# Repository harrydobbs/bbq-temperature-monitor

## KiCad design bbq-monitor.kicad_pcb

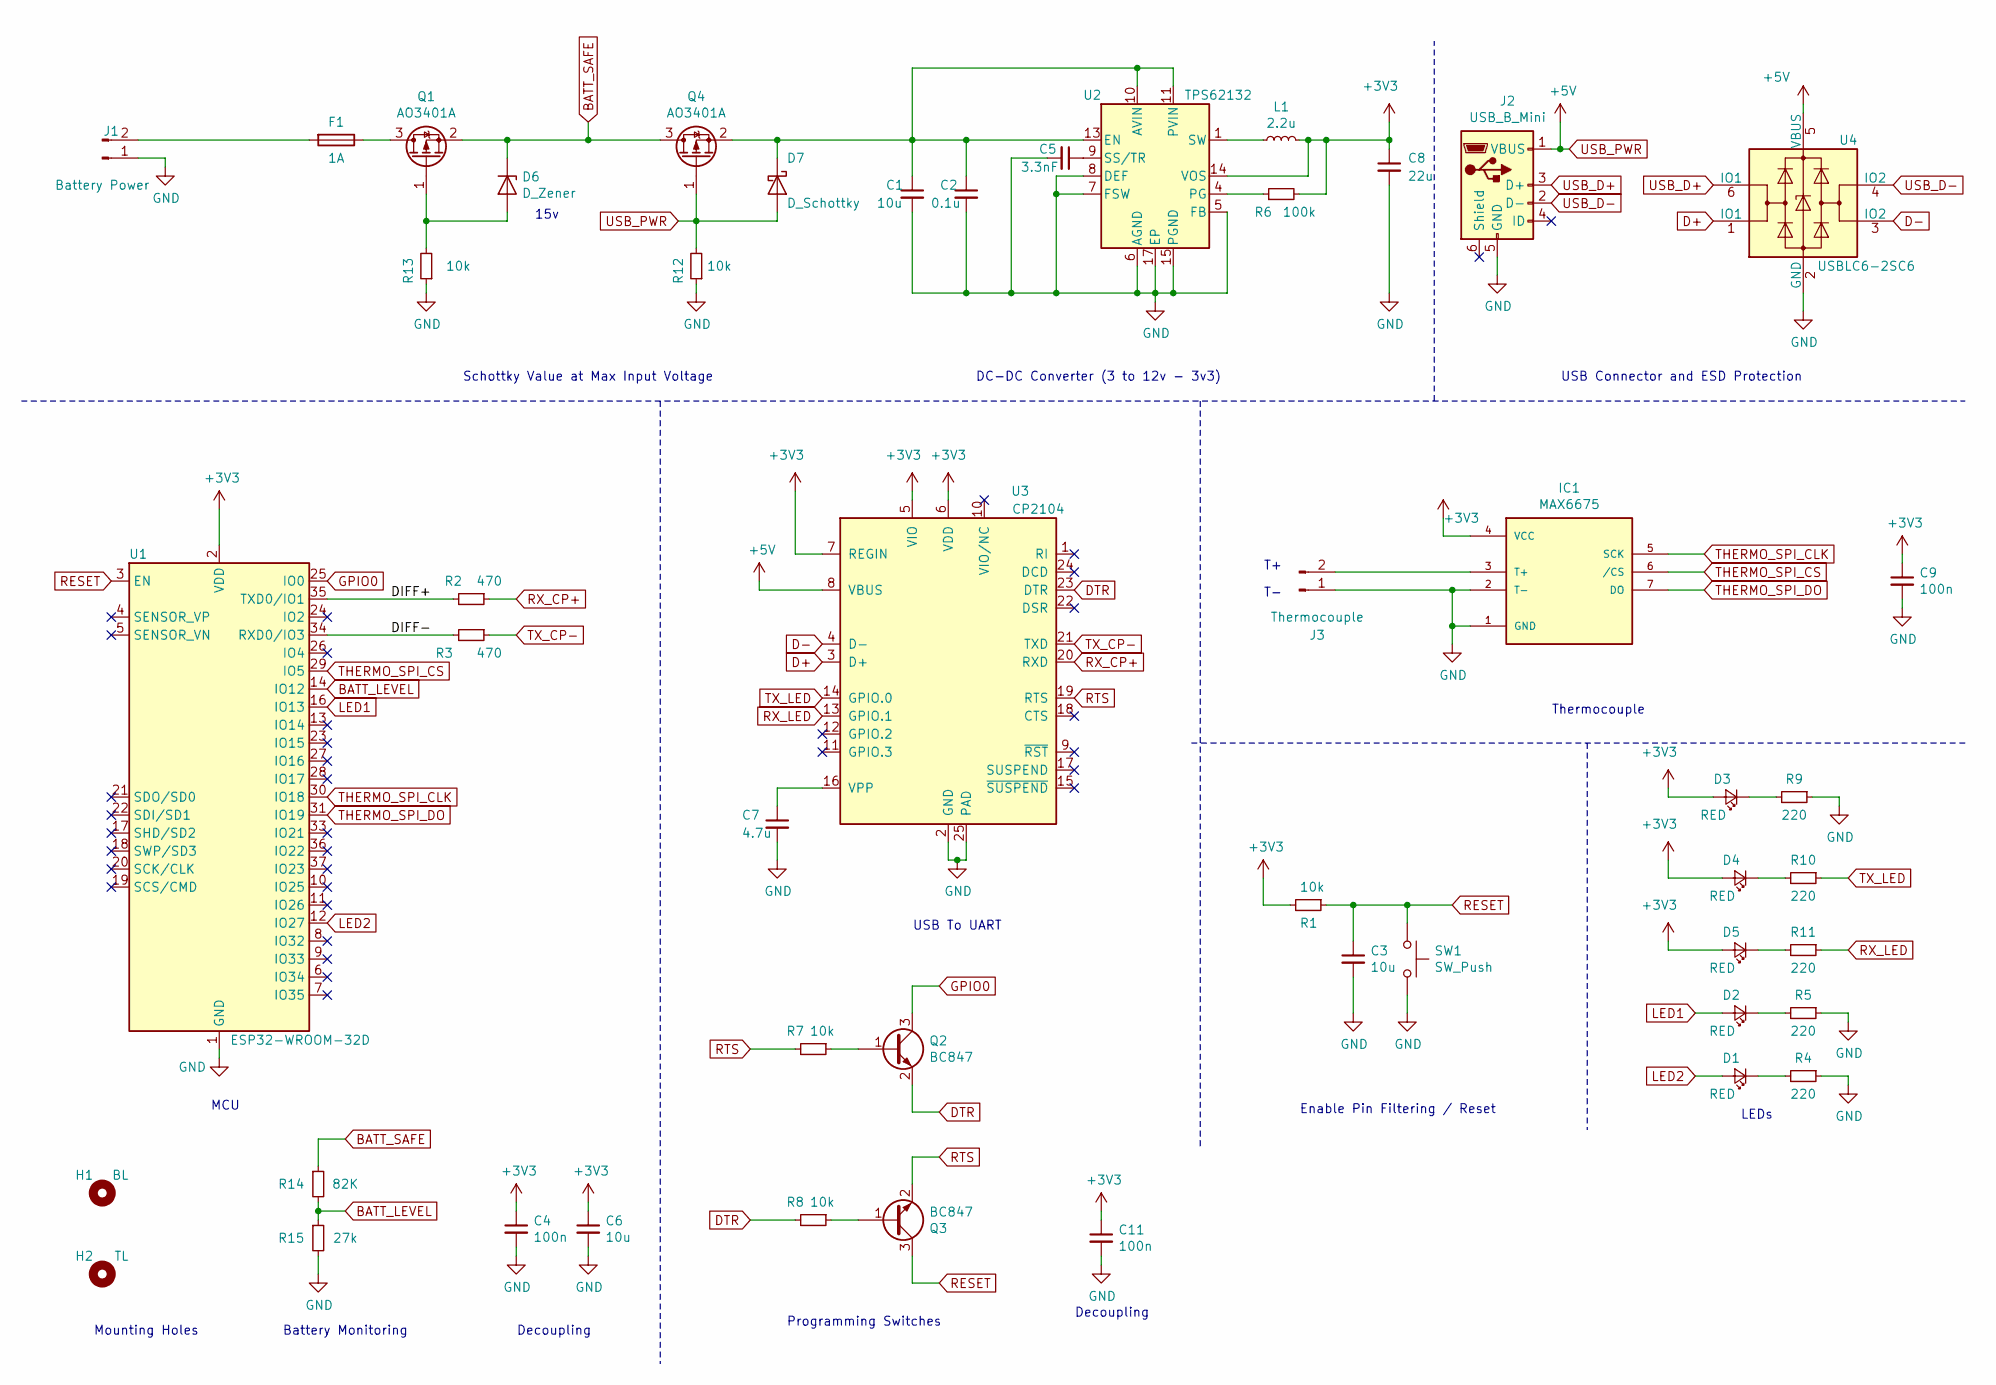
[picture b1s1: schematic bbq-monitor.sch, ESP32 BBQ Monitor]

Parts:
C1, C3, C6: 10u; C_0603_1608Metric; LCSC Part # C96446
C2: 0.1u; C_0603_1608Metric
C4, C9, C11: 100n; C_0603_1608Metric; LCSC Part # C14663
C5: 3.3nF; C_0603_1608Metric
C7: 4.7u; C_0603_1608Metric
C8: 22u; C_0603_1608Metric
D1, D2, D3, D4, D5: RED; LED_0603_1608Metric; LCSC Part # C2286
D6: D_Zener; D_1206_3216Metric
D7: D_Schottky; D_1206_3216Metric
F1: 1A; Fuse_1206_3216Metric
H1: BL; MountingHole_3.2mm_M3
H2: TL; MountingHole_3.2mm_M3
IC1: MAX6675; SO08
J1: Battery Power; RS-Pro-5mm-Pitch-2-Pin-Terminal
J2: USB_B_Mini; USB_Mini-B_Wuerth_65100516121_Horizontal
J3: Thermocouple; RS-Pro-5mm-Pitch-2-Pin-Terminal
L1: 2.2u; L_1210_3225Metric
Q1, Q4: AO3401A; SOT-23; LCSC Part # C15127
Q2, Q3: BC847; SOT-23; LCSC Part # C8664
R1, R7, R8, R12, R13: 10k; R_0603_1608Metric; LCSC Part # C25804
R2, R3: 470; R_0603_1608Metric; LCSC Part # C23179
R4, R5, R9, R10, R11: 220; R_0603_1608Metric; LCSC Part # C22962
R6: 100k; R_0603_1608Metric
R14: 82K; R_0603_1608Metric
R15: 27k; R_0603_1608Metric
SW1: SW_Push; SW_Push_1P1T_NO_6x6mm_H9.5mm
U1: ESP32-WROOM-32D; ESP32-WROOM-32; LCSC Part # C473012
U2: TPS62132; VQFN-16-1EP_3x3mm_P0.5mm_EP1.68x1.68mm_ThermalVias; LCSC Part # C81563
U3: CP2104; QFN-24-1EP_4x4mm_P0.5mm_EP2.6x2.6mm; LCSC Part # C47742 Copy
U4: USBLC6-2SC6; SOT-23-6; LCSC Part # C2827654

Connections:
+3V3: C4.1, C6.1, C8.1, C9.1, C11.1, D3.2 (A), D4.2 (A), D5.2 (A), IC1.4 (VCC), L1.2, R1.2, R6.2, U1.2 (VDD), U2.14 (VOS), U3.5 (VIO), U3.6 (VDD), U3.7 (REGIN)
/DIFF+: R2.2, U1.35 (TXD0/IO1)
/DIFF-: R3.2, U1.34 (RXD0/IO3)
BATT_LEVEL: R14.2, R15.1, U1.14 (IO12)
BATT_SAFE: D6.1 (K), Q1.2 (S), Q4.3 (D), R14.1
D+: U3.3 (D+), U4.1 (IO1)
D-: U3.4 (D-), U4.3 (IO2)
DTR: Q2.2 (E), R8.2, U3.23 (DTR)
GND: C1.2, C2.2, C3.2, C4.2, C5.2, C6.2, C7.2, C8.2, C9.2, C11.2, IC1.1 (GND), IC1.2 (T-), J1.1, J2.5 (GND), J3.1, R4.1, R5.1, R9.1, R12.1, R13.1, R15.2, SW1.2, U1.1 (GND), U1.15 (GND), U1.38 (GND), U1.39 (GND), U2.5 (FB), U2.6 (AGND), U2.7 (FSW), U2.8 (DEF), U2.15 (PGND), U2.16 (PGND), U2.17 (EP), U3.2 (GND), U3.25 (PAD), U4.2 (GND)
GPIO0: Q2.3 (C), U1.25 (IO0)
LED1: D2.2 (A), U1.16 (IO13)
LED2: D1.2 (A), U1.12 (IO27)
unnamed: C1.1, C2.1, D7.1 (K), Q4.2 (S), U2.10 (AVIN), U2.11 (PVIN), U2.12 (PVIN), U2.13 (EN)
unnamed: C5.1, U2.9 (SS/TR)
unnamed: C7.1, U3.16 (VPP)
unnamed: D1.1 (K), R4.2
unnamed: D2.1 (K), R5.2
unnamed: D3.1 (K), R9.2
unnamed: D4.1 (K), R10.2
unnamed: D5.1 (K), R11.2
unnamed: D6.2 (A), Q1.1 (G), R13.2
unnamed: F1.1, Q1.3 (D)
unnamed: F1.2, J1.2
unnamed: IC1.3 (T+), J3.2
unnamed: L1.1, U2.1 (SW), U2.2 (SW), U2.3 (SW)
unnamed: Q2.1 (B), R7.1
unnamed: Q3.1 (B), R8.1
unnamed: R6.1, U2.4 (PG)
RESET: C3.1, Q3.3 (C), R1.1, SW1.1, U1.3 (EN)
RTS: Q3.2 (E), R7.2, U3.19 (RTS)
RX_CP+: R2.1, U3.20 (RXD)
RX_LED: R11.1, U3.13 (GPIO.1)
THERMO_SPI_CLK: IC1.5 (SCK), U1.30 (IO18)
THERMO_SPI_CS: IC1.6 (/CS), U1.29 (IO5)
THERMO_SPI_DO: IC1.7 (DO), U1.31 (IO19)
TX_CP-: R3.1, U3.21 (TXD)
TX_LED: R10.1, U3.14 (GPIO.0)
USB_D+: J2.3 (D+), U4.6 (IO1)
USB_D-: J2.2 (D-), U4.4 (IO2)
USB_PWR: D7.2 (A), J2.1 (VBUS), Q4.1 (G), R12.2, U3.8 (VBUS), U4.5 (VBUS)

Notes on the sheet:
Enable Pin Filtering / Reset
USB To UART
MCU
DC-DC Converter (3 to 12v - 3v3)
Programming Switches
Decoupling
Thermocouple
USB Connector and ESD Protection
Mounting Holes
Battery Monitoring
LEDs
Schottky Value at Max Input Voltage
15v

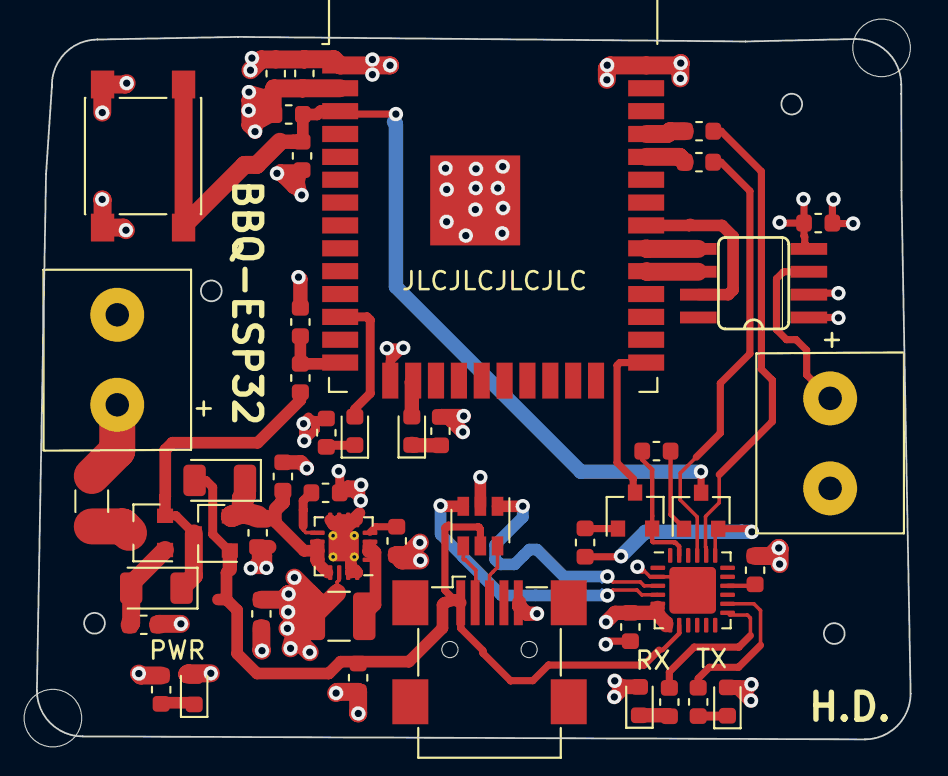
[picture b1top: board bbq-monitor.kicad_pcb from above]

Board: 4 copper layers, 48.5 x 39.0 mm, 49 parts (0 on the bottom side), 40 nets.

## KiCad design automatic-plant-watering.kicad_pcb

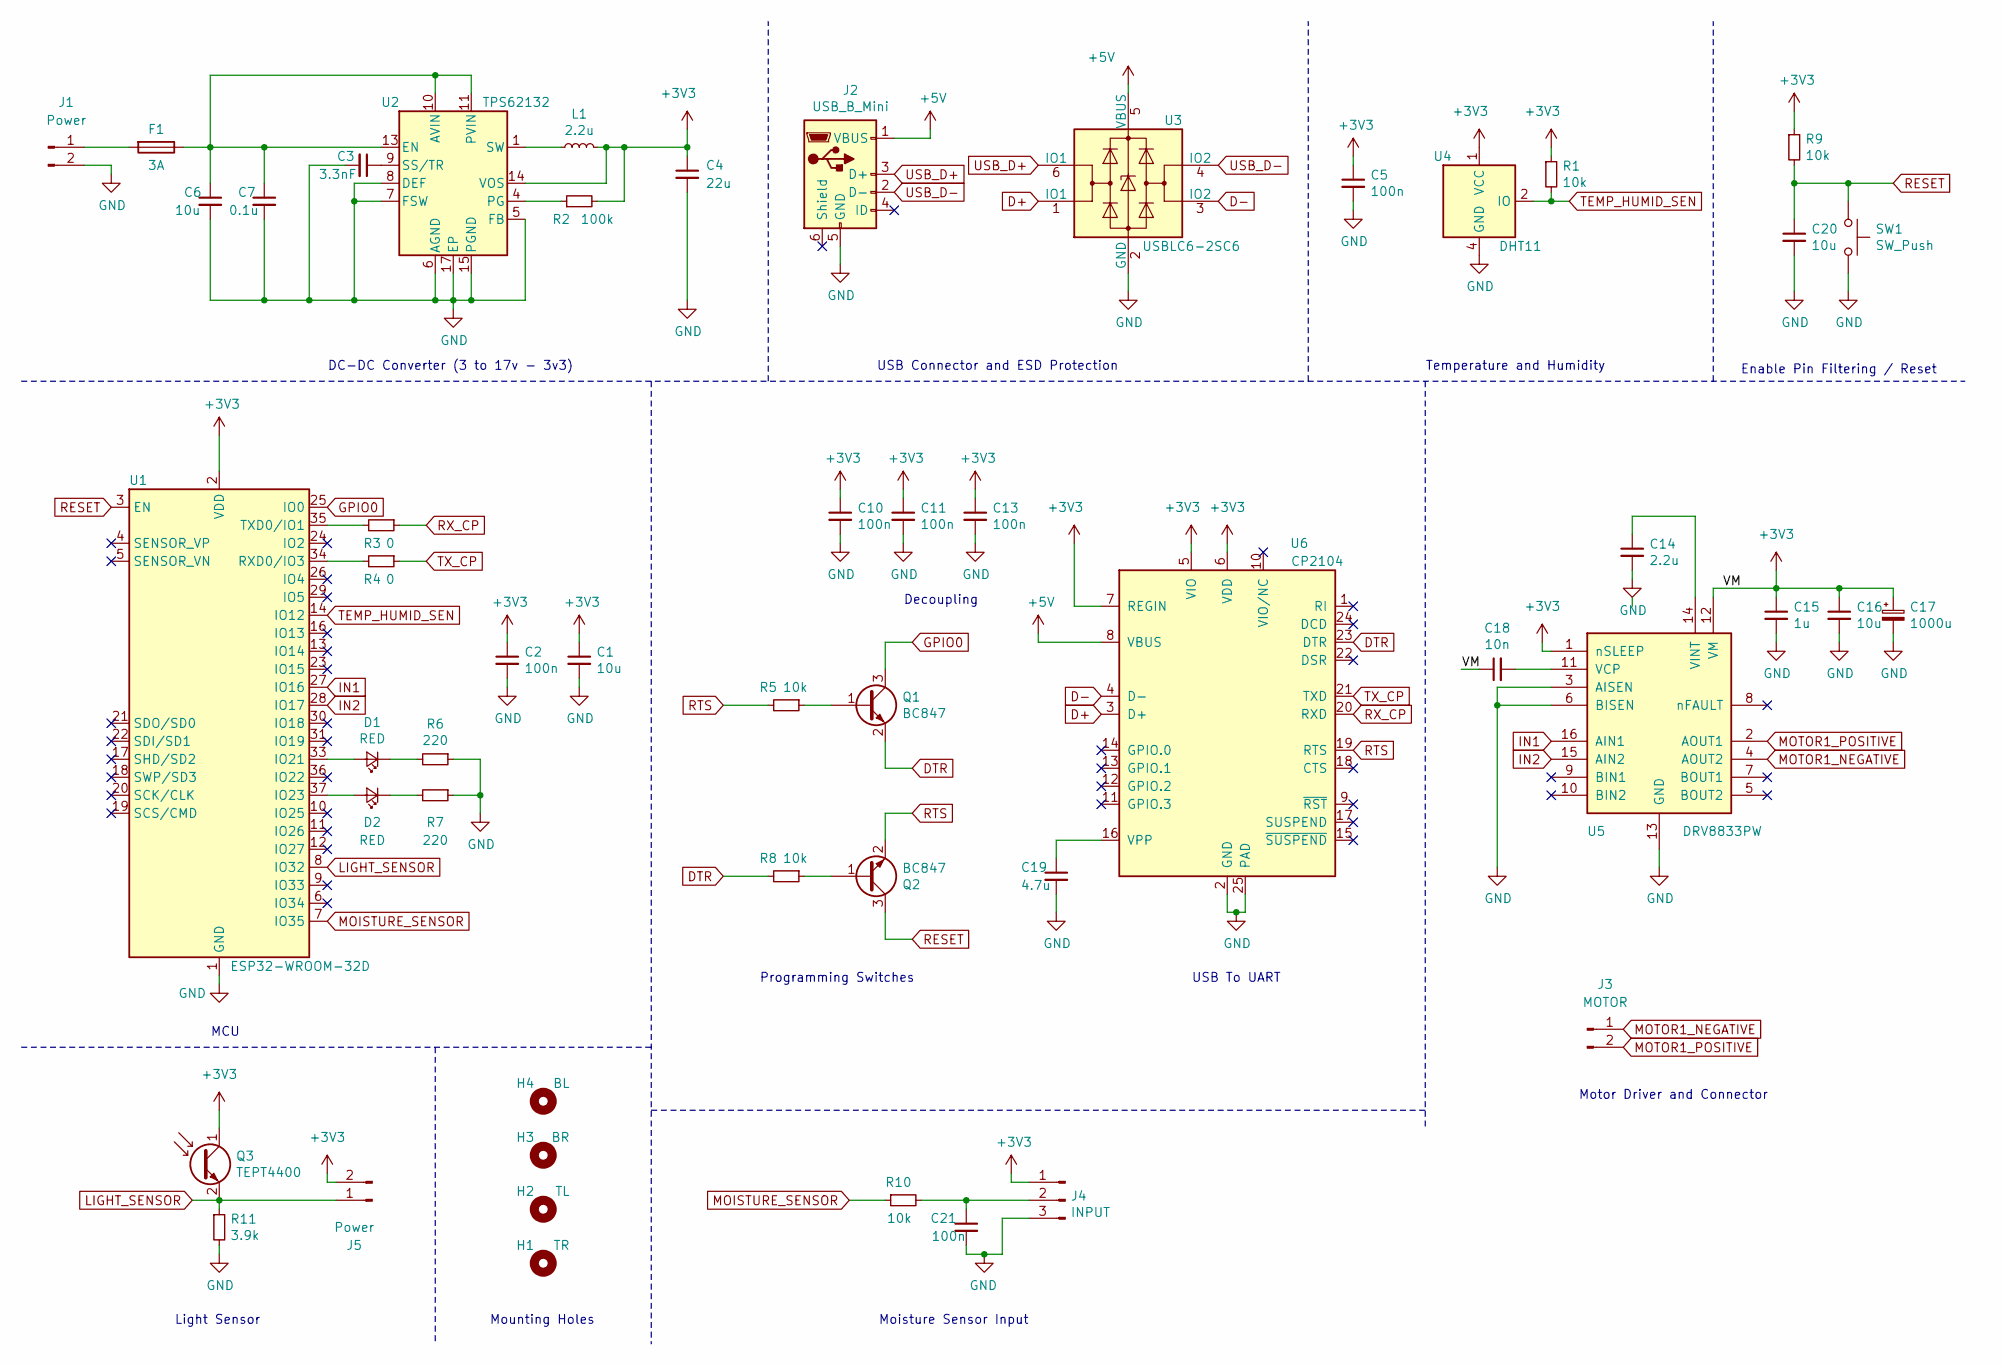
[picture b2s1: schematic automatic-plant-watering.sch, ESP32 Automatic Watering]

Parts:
C1, C6, C16, C20: 10u; C_0603_1608Metric
C2, C5, C10, C11, C13, C21: 100n; C_0603_1608Metric
C3: 3.3nF; C_0603_1608Metric
C4: 22u; C_0603_1608Metric
C7: 0.1u; C_0603_1608Metric
C14: 2.2u; C_0603_1608Metric
C15: 1u; C_0603_1608Metric
C17: 1000u; CP_Elec_10x10
C18: 10n; C_0603_1608Metric
C19: 4.7u; C_0603_1608Metric
D1, D2: RED; LED_0603_1608Metric
F1: 3A; Fuse_1206_3216Metric
H1: TR; MountingHole_4.3mm_M4_Pad_Via
H2: TL; MountingHole_4.3mm_M4_Pad_Via
H3: BR; MountingHole_4.3mm_M4_Pad_Via
H4: BL; MountingHole_4.3mm_M4_Pad_Via
J1, J5: Power; Molex_KK-254_AE-6410-02A_1x02_P2.54mm_Vertical
J2: USB_B_Mini; USB_Mini-B_Wuerth_65100516121_Horizontal
J3: MOTOR; Molex_KK-254_AE-6410-02A_1x02_P2.54mm_Vertical
J4: INPUT; Molex_KK-254_AE-6410-03A_1x03_P2.54mm_Vertical
L1: 2.2u; L_1210_3225Metric
Q1, Q2: BC847; SOT-23
Q3: TEPT4400; LED_D3.0mm_Clear
R1, R5, R8, R9, R10: 10k; R_0603_1608Metric
R2: 100k; R_0603_1608Metric
R3, R4: 0; R_0603_1608Metric
R6, R7: 220; R_0603_1608Metric
R11: 3.9k; R_0603_1608Metric
SW1: SW_Push; SW_Push_1P1T_NO_6x6mm_H9.5mm
U1: ESP32-WROOM-32D; ESP32-WROOM-32
U2: TPS62132; VQFN-16-1EP_3x3mm_P0.5mm_EP1.68x1.68mm_ThermalVias
U3: USBLC6-2SC6; SOT-23-6
U4: DHT11; Aosong_DHT11_5.5x12.0_P2.54mm
U5: DRV8833PW; TSSOP-16_4.4x5mm_P0.65mm
U6: CP2104; QFN-24-1EP_4x4mm_P0.5mm_EP2.6x2.6mm

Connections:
+3V3: C1.1, C2.1, C4.1, C5.1, C10.1, C11.1, C13.1, C15.1, C16.1, C17.1, C18.1, J4.1, J5.2, L1.2, Q3.1 (C), R1.1, R2.2, R9.1, U1.2 (VDD), U2.14 (VOS), U4.1 (VCC), U5.1 (nSLEEP), U5.12 (VM), U6.5 (VIO), U6.6 (VDD), U6.7 (REGIN)
+5V: J2.1 (VBUS), U3.5 (VBUS), U6.8 (VBUS)
D+: U3.1 (IO1), U6.3 (D+)
D-: U3.3 (IO2), U6.4 (D-)
DTR: Q1.2 (E), R8.2, U6.23 (DTR)
GND: C1.2, C2.2, C3.2, C4.2, C5.2, C6.2, C7.2, C10.2, C11.2, C13.2, C14.2, C15.2, C16.2, C17.2, C19.2, C20.2, C21.2, J1.2, J2.5 (GND), J4.3, R6.1, R7.1, R11.2, SW1.2, U1.1 (GND), U1.15 (GND), U1.38 (GND), U1.39 (GND), U2.5 (FB), U2.6 (AGND), U2.7 (FSW), U2.8 (DEF), U2.15 (PGND), U2.16 (PGND), U2.17 (EP), U3.2 (GND), U4.4 (GND), U5.3 (AISEN), U5.6 (BISEN), U5.13 (GND), U6.2 (GND), U6.25 (PAD)
GPIO0: Q1.3 (C), U1.25 (IO0)
IN1: U1.27 (IO16), U5.16 (AIN1)
IN2: U1.28 (IO17), U5.15 (AIN2)
LIGHT_SENSOR: J5.1, Q3.2 (E), R11.1, U1.8 (IO32)
MOISTURE_SENSOR: R10.1, U1.7 (IO35)
MOTOR1_NEGATIVE: J3.1, U5.4 (AOUT2)
MOTOR1_POSITIVE: J3.2, U5.2 (AOUT1)
unnamed: C3.1, U2.9 (SS/TR)
unnamed: C6.1, C7.1, F1.1, U2.10 (AVIN), U2.11 (PVIN), U2.12 (PVIN), U2.13 (EN)
unnamed: C14.1, U5.14 (VINT)
unnamed: C18.2, U5.11 (VCP)
unnamed: C19.1, U6.16 (VPP)
unnamed: C21.1, J4.2, R10.2
unnamed: D1.1 (K), R6.2
unnamed: D1.2 (A), U1.33 (IO21)
unnamed: D2.1 (K), R7.2
unnamed: D2.2 (A), U1.37 (IO23)
unnamed: F1.2, J1.1
unnamed: L1.1, U2.1 (SW), U2.2 (SW), U2.3 (SW)
unnamed: Q1.1 (B), R5.1
unnamed: Q2.1 (B), R8.1
unnamed: R2.1, U2.4 (PG)
unnamed: R3.2, U1.35 (TXD0/IO1)
unnamed: R4.2, U1.34 (RXD0/IO3)
RESET: C20.1, Q2.3 (C), R9.2, SW1.1, U1.3 (EN)
RTS: Q2.2 (E), R5.2, U6.19 (RTS)
RX_CP: R3.1, U6.20 (RXD)
TEMP_HUMID_SEN: R1.2, U1.14 (IO12), U4.2 (IO)
TX_CP: R4.1, U6.21 (TXD)
USB_D+: J2.3 (D+), U3.6 (IO1)
USB_D-: J2.2 (D-), U3.4 (IO2)

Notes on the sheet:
Enable Pin Filtering / Reset
USB To UART
MCU
Motor Driver and Connector
Temperature and Humidity
DC-DC Converter (3 to 17v - 3v3)
Programming Switches
Decoupling
Light Sensor
Moisture Sensor Input
USB Connector and ESD Protection
Mounting Holes

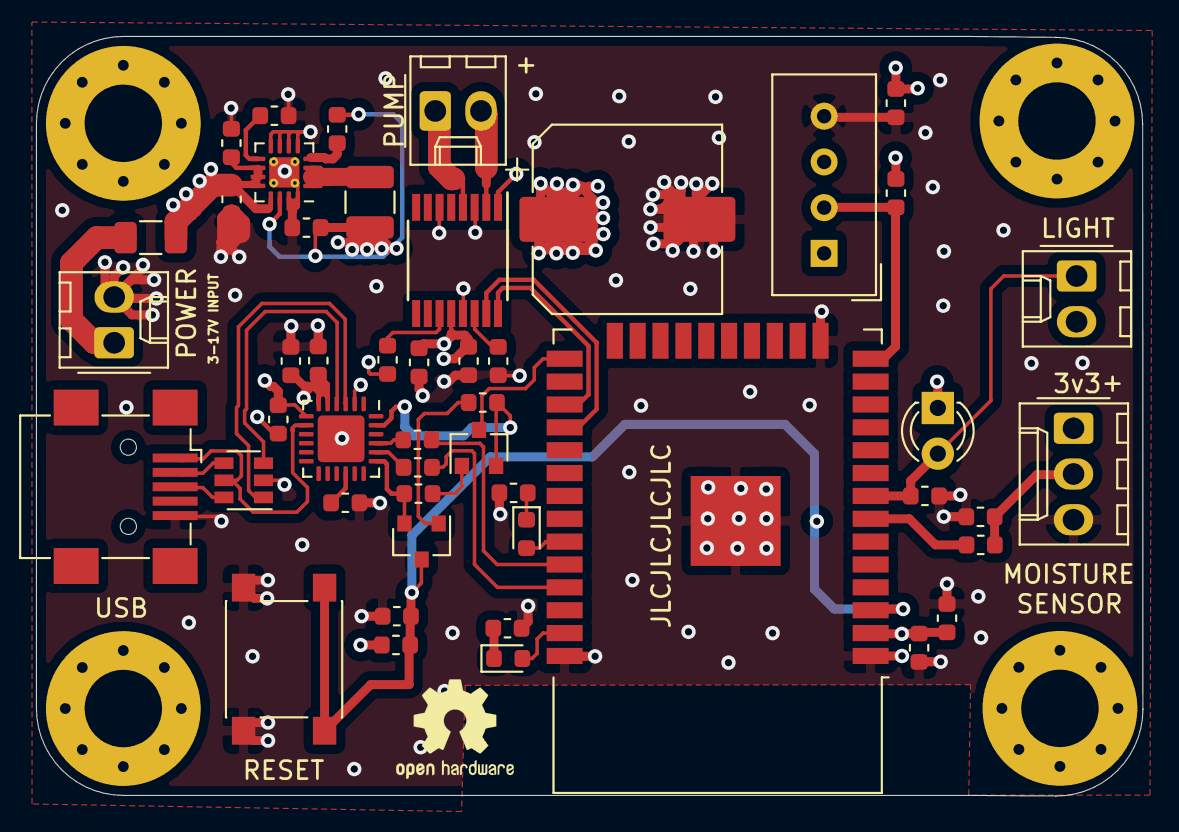
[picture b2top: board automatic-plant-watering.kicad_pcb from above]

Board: 4 copper layers, 61.5 x 42.2 mm, 52 parts (0 on the bottom side), 37 nets.

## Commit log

2021-04-04 inital commit
2021-08-26 pcb draft finished
2021-08-26 minor tidy up
2021-08-26 Gave it a bit of a tidy up
2021-09-07 updated gerbers
2022-06-23 Commiting before I remove hard to source components
2022-06-24 dc-dc is too expexpesnive - project is on hold
